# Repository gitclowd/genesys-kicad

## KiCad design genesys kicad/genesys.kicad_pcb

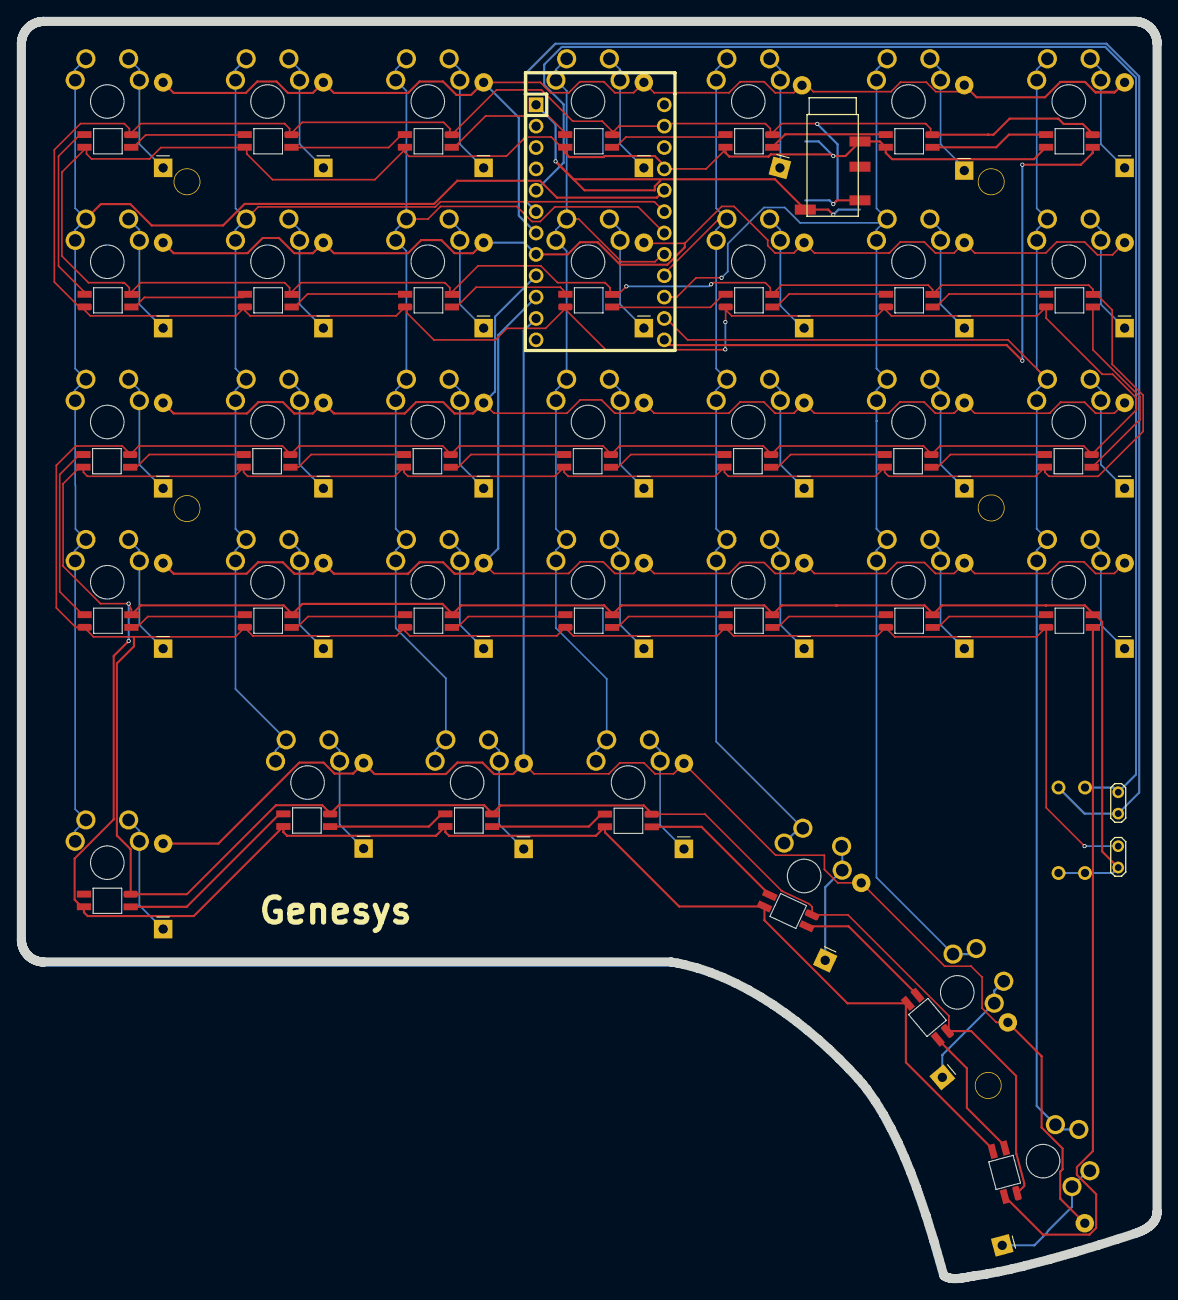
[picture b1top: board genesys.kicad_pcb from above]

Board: 2 copper layers, 135.0 x 149.5 mm, 117 parts (1 on the bottom side), 87 nets.

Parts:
D1, D2, D3, D4, D5, D6, D7, D8, D9, D10, D11, D12, D13, D14, D15, D16, D17, D18, D19, D20, D21, D22, D23, D24, D25, D26, D27, D28, D29, D30, D31, D32, D33, D34, D35: DIODE; D_DO-41_SOD81_P10.16mm_Genesys
H1, H2, H4, H5, H7: MountingHole_Pad; MountingHole_3mm
J1, J2: AudioJack4; TRRS-PJ-320D_genesys
R1, R2: R; Resistor
SK6812Mini-E1, SK6812Mini-E2, SK6812Mini-E3, SK6812Mini-E4, SK6812Mini-E5, SK6812Mini-E6, SK6812Mini-E7, SK6812Mini-E8, SK6812Mini-E9, SK6812Mini-E10, SK6812Mini-E11, SK6812Mini-E12, SK6812Mini-E13, SK6812Mini-E14, SK6812Mini-E15, SK6812Mini-E16, SK6812Mini-E17, SK6812Mini-E18, SK6812Mini-E19, SK6812Mini-E20, SK6812Mini-E21, SK6812Mini-E22, SK6812Mini-E23, SK6812Mini-E24, SK6812Mini-E25, SK6812Mini-E26, SK6812Mini-E27, SK6812Mini-E28, SK6812Mini-E29, SK6812Mini-E30, SK6812Mini-E31, SK6812Mini-E32, SK6812Mini-E33, SK6812Mini-E34, SK6812Mini-E35: SK6812-MINI-E
SW1, SW2, SW3, SW4, SW5, SW6, SW7, SW8, SW9, SW10, SW11, SW12, SW13, SW14, SW15, SW16, SW17, SW18, SW19, SW20, SW21, SW22, SW23, SW24, SW25, SW26, SW27, SW28, SW29, SW30, SW31, SW32, SW33, SW34, SW35: SW_MX; SW_MX_reversible_minimal
TP3: Cirque I2C; TestPoint_2Pads_Pitch2.54mm_Drill0.8mm
TP4: Cirque PWR; TestPoint_2Pads_Pitch2.54mm_Drill0.8mm
U1: ProMicro; ArduinoProMicro

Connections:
/Col0: SW1.1, SW8.1, SW15.1, SW22.1, SW29.1, U1.20 (F4)
/Col1: SW2.1, SW9.1, SW16.1, SW23.1, SW30.1, U1.19 (F5)
/Col2: SW3.1, SW10.1, SW17.1, SW24.1, SW31.1, U1.18 (F6)
/Col3: SW4.1, SW11.1, SW18.1, SW25.1, SW32.1, U1.17 (F7)
/Col4: SW5.1, SW12.1, SW19.1, SW26.1, SW33.1, U1.16 (B1)
/Col5: SW6.1, SW13.1, SW20.1, SW27.1, SW34.1, U1.15 (B3)
/Col6: SW7.1, SW14.1, SW21.1, SW28.1, SW35.1, U1.14 (B2)
/LED_5V: J1.S, J2.S, R1.2, R2.2, SK6812Mini-E1.1 (VSS), SK6812Mini-E2.1 (VSS), SK6812Mini-E3.1 (VSS), SK6812Mini-E4.1 (VSS), SK6812Mini-E5.1 (VSS), SK6812Mini-E6.1 (VSS), SK6812Mini-E7.1 (VSS), SK6812Mini-E8.1 (VSS), SK6812Mini-E9.1 (VSS), SK6812Mini-E10.1 (VSS), SK6812Mini-E11.1 (VSS), SK6812Mini-E12.1 (VSS), SK6812Mini-E13.1 (VSS), SK6812Mini-E14.1 (VSS), SK6812Mini-E15.1 (VSS), SK6812Mini-E16.1 (VSS), SK6812Mini-E17.1 (VSS), SK6812Mini-E18.1 (VSS), SK6812Mini-E19.1 (VSS), SK6812Mini-E20.1 (VSS), SK6812Mini-E21.1 (VSS), SK6812Mini-E22.1 (VSS), SK6812Mini-E23.1 (VSS), SK6812Mini-E24.1 (VSS), SK6812Mini-E25.1 (VSS), SK6812Mini-E26.1 (VSS), SK6812Mini-E27.1 (VSS), SK6812Mini-E28.1 (VSS), SK6812Mini-E29.1 (VSS), SK6812Mini-E30.1 (VSS), SK6812Mini-E31.1 (VSS), SK6812Mini-E32.1 (VSS), SK6812Mini-E33.1 (VSS), SK6812Mini-E34.1 (VSS), SK6812Mini-E35.1 (VSS), TP4.1, U1.21 (VCC)
/LED_DIN: SK6812Mini-E1.4 (DIN), U1.13 (B6)
/LED_GND: J1.R1, J2.R1, SK6812Mini-E1.3 (VDD), SK6812Mini-E2.3 (VDD), SK6812Mini-E3.3 (VDD), SK6812Mini-E4.3 (VDD), SK6812Mini-E5.3 (VDD), SK6812Mini-E6.3 (VDD), SK6812Mini-E7.3 (VDD), SK6812Mini-E8.3 (VDD), SK6812Mini-E9.3 (VDD), SK6812Mini-E10.3 (VDD), SK6812Mini-E11.3 (VDD), SK6812Mini-E12.3 (VDD), SK6812Mini-E13.3 (VDD), SK6812Mini-E14.3 (VDD), SK6812Mini-E15.3 (VDD), SK6812Mini-E16.3 (VDD), SK6812Mini-E17.3 (VDD), SK6812Mini-E18.3 (VDD), SK6812Mini-E19.3 (VDD), SK6812Mini-E20.3 (VDD), SK6812Mini-E21.3 (VDD), SK6812Mini-E22.3 (VDD), SK6812Mini-E23.3 (VDD), SK6812Mini-E24.3 (VDD), SK6812Mini-E25.3 (VDD), SK6812Mini-E26.3 (VDD), SK6812Mini-E27.3 (VDD), SK6812Mini-E28.3 (VDD), SK6812Mini-E29.3 (VDD), SK6812Mini-E30.3 (VDD), SK6812Mini-E31.3 (VDD), SK6812Mini-E32.3 (VDD), SK6812Mini-E33.3 (VDD), SK6812Mini-E34.3 (VDD), SK6812Mini-E35.3 (VDD), TP4.2, U1.23 (GND)
/Row0: D1.2 (K), D2.2 (K), D3.2 (K), D4.2 (K), D5.2 (K), D6.2 (K), D7.2 (K), U1.7 (D4)
/Row1: D8.2 (K), D9.2 (K), D10.2 (K), D11.2 (K), D12.2 (K), D13.2 (K), D14.2 (K), U1.8 (C6)
/Row2: D15.2 (K), D16.2 (K), D17.2 (K), D18.2 (K), D19.2 (K), D20.2 (K), D21.2 (K), U1.9 (D7)
/Row3: D22.2 (K), D23.2 (K), D24.2 (K), D25.2 (K), D26.2 (K), D27.2 (K), D28.2 (K), U1.10 (E6)
/Row4: D29.2 (K), D30.2 (K), D31.2 (K), D32.2 (K), D33.2 (K), D34.2 (K), D35.2 (K), U1.11 (B4)
/SCL: R2.1, TP3.2, U1.6 (SCL)
/SDA: R1.1, TP3.1, U1.5 (SDA)
/SERIAL: J1.T, J2.T, U1.1 (TX)
unnamed: D1.1 (A), SW1.2
unnamed: D2.1 (A), SW2.2
unnamed: D3.1 (A), SW3.2
unnamed: D4.1 (A), SW4.2
unnamed: D5.1 (A), SW5.2
unnamed: D6.1 (A), SW6.2
unnamed: D7.1 (A), SW7.2
unnamed: D8.1 (A), SW8.2
unnamed: D9.1 (A), SW9.2
unnamed: D10.1 (A), SW10.2
unnamed: D11.1 (A), SW11.2
unnamed: D12.1 (A), SW12.2
unnamed: D13.1 (A), SW13.2
unnamed: D14.1 (A), SW14.2
unnamed: D15.1 (A), SW15.2
unnamed: D16.1 (A), SW16.2
unnamed: D17.1 (A), SW17.2
unnamed: D18.1 (A), SW18.2
unnamed: D19.1 (A), SW19.2
unnamed: D20.1 (A), SW20.2
unnamed: D21.1 (A), SW21.2
unnamed: D22.1 (A), SW22.2
unnamed: D23.1 (A), SW23.2
unnamed: D24.1 (A), SW24.2
unnamed: D25.1 (A), SW25.2
unnamed: D26.1 (A), SW26.2
unnamed: D27.1 (A), SW27.2
unnamed: D28.1 (A), SW28.2
unnamed: D29.1 (A), SW29.2
unnamed: D30.1 (A), SW30.2
unnamed: D31.1 (A), SW31.2
unnamed: D32.1 (A), SW32.2
unnamed: D33.1 (A), SW33.2
unnamed: D34.1 (A), SW34.2
unnamed: D35.1 (A), SW35.2
unnamed: SK6812Mini-E1.2 (DOUT), SK6812Mini-E2.4 (DIN)
unnamed: SK6812Mini-E2.2 (DOUT), SK6812Mini-E3.4 (DIN)
unnamed: SK6812Mini-E3.2 (DOUT), SK6812Mini-E4.4 (DIN)
unnamed: SK6812Mini-E4.2 (DOUT), SK6812Mini-E5.4 (DIN)
unnamed: SK6812Mini-E5.2 (DOUT), SK6812Mini-E6.4 (DIN)
unnamed: SK6812Mini-E6.2 (DOUT), SK6812Mini-E7.4 (DIN)
unnamed: SK6812Mini-E7.2 (DOUT), SK6812Mini-E8.4 (DIN)
unnamed: SK6812Mini-E8.2 (DOUT), SK6812Mini-E9.4 (DIN)
unnamed: SK6812Mini-E9.2 (DOUT), SK6812Mini-E10.4 (DIN)
unnamed: SK6812Mini-E10.2 (DOUT), SK6812Mini-E11.4 (DIN)
unnamed: SK6812Mini-E11.2 (DOUT), SK6812Mini-E12.4 (DIN)
unnamed: SK6812Mini-E12.2 (DOUT), SK6812Mini-E13.4 (DIN)
unnamed: SK6812Mini-E13.2 (DOUT), SK6812Mini-E14.4 (DIN)
unnamed: SK6812Mini-E14.2 (DOUT), SK6812Mini-E15.4 (DIN)
unnamed: SK6812Mini-E15.2 (DOUT), SK6812Mini-E16.4 (DIN)
unnamed: SK6812Mini-E16.2 (DOUT), SK6812Mini-E17.4 (DIN)
unnamed: SK6812Mini-E17.2 (DOUT), SK6812Mini-E18.4 (DIN)
unnamed: SK6812Mini-E18.2 (DOUT), SK6812Mini-E19.4 (DIN)
unnamed: SK6812Mini-E19.2 (DOUT), SK6812Mini-E20.4 (DIN)
unnamed: SK6812Mini-E20.2 (DOUT), SK6812Mini-E21.4 (DIN)
unnamed: SK6812Mini-E21.2 (DOUT), SK6812Mini-E22.4 (DIN)
unnamed: SK6812Mini-E22.2 (DOUT), SK6812Mini-E23.4 (DIN)
unnamed: SK6812Mini-E23.2 (DOUT), SK6812Mini-E24.4 (DIN)
unnamed: SK6812Mini-E24.2 (DOUT), SK6812Mini-E25.4 (DIN)
unnamed: SK6812Mini-E25.2 (DOUT), SK6812Mini-E26.4 (DIN)
unnamed: SK6812Mini-E26.2 (DOUT), SK6812Mini-E27.4 (DIN)
unnamed: SK6812Mini-E27.2 (DOUT), SK6812Mini-E28.4 (DIN)
unnamed: SK6812Mini-E28.2 (DOUT), SK6812Mini-E29.4 (DIN)
unnamed: SK6812Mini-E29.2 (DOUT), SK6812Mini-E30.4 (DIN)
unnamed: SK6812Mini-E30.2 (DOUT), SK6812Mini-E31.4 (DIN)
unnamed: SK6812Mini-E31.2 (DOUT), SK6812Mini-E32.4 (DIN)
unnamed: SK6812Mini-E32.2 (DOUT), SK6812Mini-E33.4 (DIN)
unnamed: SK6812Mini-E33.2 (DOUT), SK6812Mini-E34.4 (DIN)
unnamed: SK6812Mini-E34.2 (DOUT), SK6812Mini-E35.4 (DIN)
